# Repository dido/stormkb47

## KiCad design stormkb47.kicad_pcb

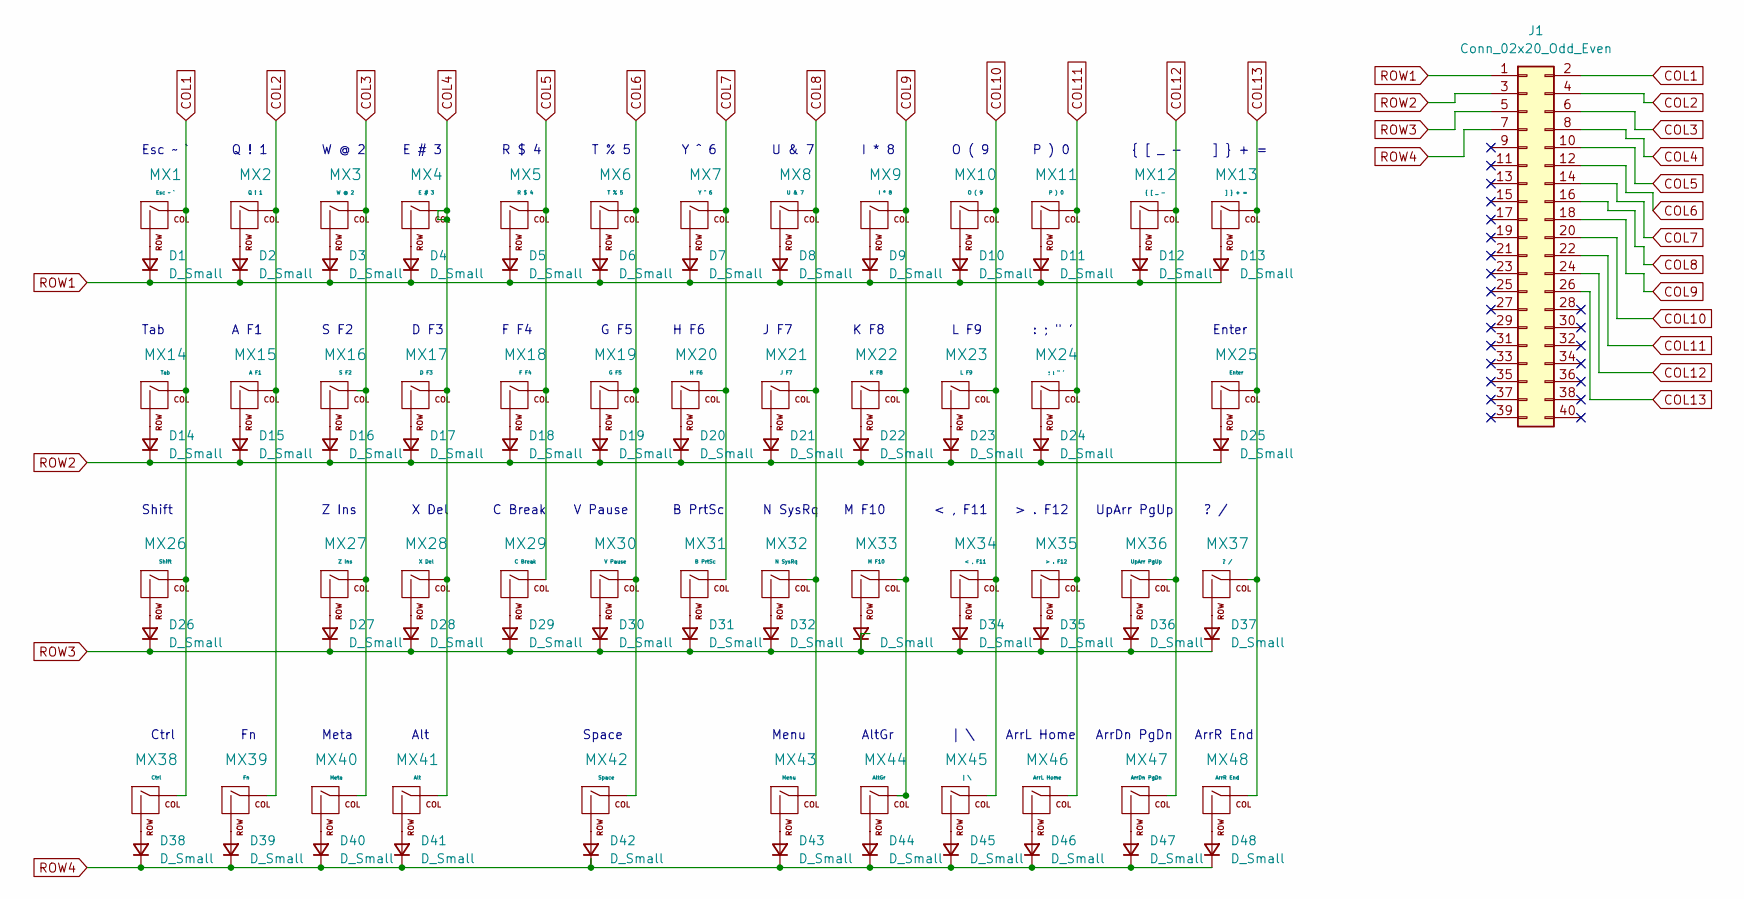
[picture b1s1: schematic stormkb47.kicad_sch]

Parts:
D1, D2, D3, D4, D5, D6, D7, D8, D9, D10, D11, D12, D13, D14, D15, D16, D17, D18, D19, D20, D21, D22, D23, D24, D25, D26, D27, D28, D29, D30, D31, D32, D33, D34, D35, D36, D37, D38, D39, D40, D41, D42, D43, D44, D45, D46, D47, D48: D_Small; D_SOD-123
J1: Conn_02x20_Odd_Even; PinSocket_2x20_P2.54mm_Vertical
MX1: Esc ~ `; MX-1U-NoLED
MX2: Q ! 1; MX-1U-NoLED
MX3: W @ 2; MX-1U-NoLED
MX4: E # 3; MX-1U-NoLED
MX5: R $ 4; MX-1U-NoLED
MX6: T % 5; MX-1U-NoLED
MX7: Y ^ 6; MX-1U-NoLED
MX8: U & 7; MX-1U-NoLED
MX9: I * 8; MX-1U-NoLED
MX10: O ( 9; MX-1U-NoLED
MX11: P ) 0; MX-1U-NoLED
MX12: { [ _ -; MX-1U-NoLED
MX13: ] } + =; MX-1U-NoLED
MX14: Tab; MX-1.5U-NoLED
MX15: A F1; MX-1U-NoLED
MX16: S F2; MX-1U-NoLED
MX17: D F3; MX-1U-NoLED
MX18: F F4; MX-1U-NoLED
MX19: G F5; MX-1U-NoLED
MX20: H F6; MX-1U-NoLED
MX21: J F7; MX-1U-NoLED
MX22: K F8; MX-1U-NoLED
MX23: L F9; MX-1U-NoLED
MX24: ; : " '; MX-1U-NoLED
MX25: Enter; MX-1.5U-NoLED
MX26: Shift; MX-2U-NoLED
MX27: Z Ins; MX-1U-NoLED
MX28: X Del; MX-1U-NoLED
MX29: C Break; MX-1U-NoLED
MX30: V Pause; MX-1U-NoLED
MX31: B PrtSc; MX-1U-NoLED
MX32: N SysRq; MX-1U-NoLED
MX33: M F10; MX-1U-NoLED
MX34: < , F11; MX-1U-NoLED
MX35: > . F12; MX-1U-NoLED
MX36: UpArr PgUp; MX-1U-NoLED
MX37: ? /; MX-1U-NoLED
MX38: Ctrl; MX-1U-NoLED
MX39: Fn; MX-1U-NoLED
MX40: Meta; MX-1U-NoLED
MX41: Alt; MX-1U-NoLED
MX42: Space; MX-3U-NoLED
MX43: Menu; MX-1U-NoLED
MX44: AltGr; MX-1U-NoLED
MX45: | \; MX-1U-NoLED
MX46: ArrL Home; MX-1U-NoLED
MX47: ArrDn PgDn; MX-1U-NoLED
MX48: ArrR End; MX-1U-NoLED

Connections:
COL1: J1.2, MX1.1 (COL), MX14.1 (COL), MX26.1 (COL), MX38.1 (COL)
COL2: J1.4, MX2.1 (COL), MX15.1 (COL), MX39.1 (COL)
COL3: J1.6, MX3.1 (COL), MX16.1 (COL), MX27.1 (COL), MX40.1 (COL)
COL4: J1.8, MX4.1 (COL), MX17.1 (COL), MX28.1 (COL), MX41.1 (COL)
COL5: J1.10, MX5.1 (COL), MX18.1 (COL), MX29.1 (COL)
COL6: J1.12, MX6.1 (COL), MX19.1 (COL), MX30.1 (COL), MX42.1 (COL)
COL7: J1.14, MX7.1 (COL), MX20.1 (COL), MX31.1 (COL)
COL8: J1.16, MX8.1 (COL), MX21.1 (COL), MX32.1 (COL), MX43.1 (COL)
COL9: J1.18, MX9.1 (COL), MX22.1 (COL), MX33.1 (COL), MX44.1 (COL)
COL10: J1.20, MX10.1 (COL), MX23.1 (COL), MX34.1 (COL), MX45.1 (COL)
COL11: J1.22, MX11.1 (COL), MX24.1 (COL), MX35.1 (COL), MX46.1 (COL)
COL12: J1.24, MX12.1 (COL), MX36.1 (COL), MX47.1 (COL)
COL13: J1.26, MX13.1 (COL), MX25.1 (COL), MX37.1 (COL), MX48.1 (COL)
unnamed: D1.2 (A), MX1.2 (ROW)
unnamed: D2.2 (A), MX2.2 (ROW)
unnamed: D3.2 (A), MX3.2 (ROW)
unnamed: D4.2 (A), MX4.2 (ROW)
unnamed: D5.2 (A), MX5.2 (ROW)
unnamed: D6.2 (A), MX6.2 (ROW)
unnamed: D7.2 (A), MX7.2 (ROW)
unnamed: D8.2 (A), MX8.2 (ROW)
unnamed: D9.2 (A), MX9.2 (ROW)
unnamed: D10.2 (A), MX10.2 (ROW)
unnamed: D11.2 (A), MX11.2 (ROW)
unnamed: D12.2 (A), MX12.2 (ROW)
unnamed: D13.2 (A), MX13.2 (ROW)
unnamed: D14.2 (A), MX14.2 (ROW)
unnamed: D15.2 (A), MX15.2 (ROW)
unnamed: D16.2 (A), MX16.2 (ROW)
unnamed: D17.2 (A), MX17.2 (ROW)
unnamed: D18.2 (A), MX18.2 (ROW)
unnamed: D19.2 (A), MX19.2 (ROW)
unnamed: D20.2 (A), MX20.2 (ROW)
unnamed: D21.2 (A), MX21.2 (ROW)
unnamed: D22.2 (A), MX22.2 (ROW)
unnamed: D23.2 (A), MX23.2 (ROW)
unnamed: D24.2 (A), MX24.2 (ROW)
unnamed: D25.2 (A), MX25.2 (ROW)
unnamed: D26.2 (A), MX26.2 (ROW)
unnamed: D27.2 (A), MX27.2 (ROW)
unnamed: D28.2 (A), MX28.2 (ROW)
unnamed: D29.2 (A), MX29.2 (ROW)
unnamed: D30.2 (A), MX30.2 (ROW)
unnamed: D31.2 (A), MX31.2 (ROW)
unnamed: D32.2 (A), MX32.2 (ROW)
unnamed: D33.2 (A), MX33.2 (ROW)
unnamed: D34.2 (A), MX34.2 (ROW)
unnamed: D35.2 (A), MX35.2 (ROW)
unnamed: D36.2 (A), MX36.2 (ROW)
unnamed: D37.2 (A), MX37.2 (ROW)
unnamed: D38.2 (A), MX38.2 (ROW)
unnamed: D39.2 (A), MX39.2 (ROW)
unnamed: D40.2 (A), MX40.2 (ROW)
unnamed: D41.2 (A), MX41.2 (ROW)
unnamed: D42.2 (A), MX42.2 (ROW)
unnamed: D43.2 (A), MX43.2 (ROW)
unnamed: D44.2 (A), MX44.2 (ROW)
unnamed: D45.2 (A), MX45.2 (ROW)
unnamed: D46.2 (A), MX46.2 (ROW)
unnamed: D47.2 (A), MX47.2 (ROW)
unnamed: D48.2 (A), MX48.2 (ROW)
ROW1: D1.1 (K), D2.1 (K), D3.1 (K), D4.1 (K), D5.1 (K), D6.1 (K), D7.1 (K), D8.1 (K), D9.1 (K), D10.1 (K), D11.1 (K), D12.1 (K), D13.1 (K), J1.1
ROW2: D14.1 (K), D15.1 (K), D16.1 (K), D17.1 (K), D18.1 (K), D19.1 (K), D20.1 (K), D21.1 (K), D22.1 (K), D23.1 (K), D24.1 (K), D25.1 (K), J1.3
ROW3: D26.1 (K), D27.1 (K), D28.1 (K), D29.1 (K), D30.1 (K), D31.1 (K), D32.1 (K), D33.1 (K), D34.1 (K), D35.1 (K), D36.1 (K), D37.1 (K), J1.5
ROW4: D38.1 (K), D39.1 (K), D40.1 (K), D41.1 (K), D42.1 (K), D43.1 (K), D44.1 (K), D45.1 (K), D46.1 (K), D47.1 (K), D48.1 (K), J1.7

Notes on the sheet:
M F10
H F6
G F5
Tab
I * 8
A F1
UpArr PgUp
Alt
| \
{ [ _ -
> . F12
Esc ~ `
W @ 2
B PrtSc
? /
F F4
: ; " '
R $ 4
U & 7
Enter
Meta
J F7
] } + =
X Del
V Pause
ArrDn PgDn
< , F11
S F2
Q ! 1
T % 5
Y ^ 6
N SysRq
Menu
L F9
ArrR End
O ( 9
Ctrl
Z Ins
E # 3
ArrL Home

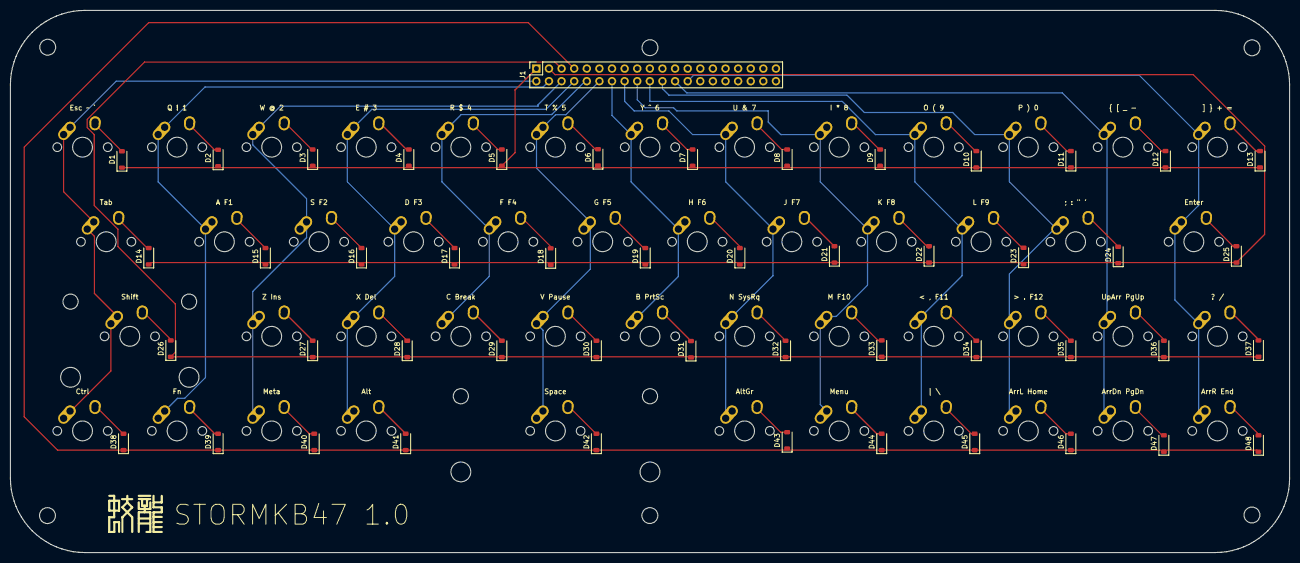
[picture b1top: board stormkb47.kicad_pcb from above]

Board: 2 copper layers, 257.7 x 109.2 mm, 97 parts (0 on the bottom side), 65 nets.

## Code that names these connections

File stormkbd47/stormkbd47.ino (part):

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// Arduino pins associated with columns and rows for the
// keyboard matrix

const byte col1 = A4;
const byte col2 = 2;
const byte col3 = 3;
const byte col4 = 4;
const byte col5 = 5;
const byte col6 = 6;
const byte col7 = 7;
const byte col8 = 8;
const byte col9 = 9;
const byte col10 = 10;
const byte col11 = 11;
const byte col12 = 12;
const byte col13 = 13;

const byte row1 = A0;
const byte row2 = A1;
const byte row3 = A2;
const byte row4 = A3;

#define USE_KEYBOARD
#define USE_LED
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  digitalWrite(row3, LOW); // turn off pullup
  digitalWrite(row4, LOW); // turn off pullup

  pinMode(row1, INPUT); // High-Z
  pinMode(row2, INPUT); // High-Z 
  pinMode(row3, INPUT); // High-Z
  pinMode(row4, INPUT); // High-Z
  
  // Rows are inputs with pullups
  
  pinMode(row1, INPUT);
  pinMode(row2, INPUT);
  pinMode(row3, INPUT);
  pinMode(row4, INPUT);

  pinMode(col1, INPUT);
  pinMode(col2, INPUT);
  pinMode(col3, INPUT);
  pinMode(col4, INPUT);
  pinMode(col5, INPUT);
  pinMode(col6, INPUT);
  pinMode(col7, INPUT);
  pinMode(col8, INPUT);
  pinMode(col9, INPUT);
  pinMode(col10, INPUT);
  pinMode(col11, INPUT);
  pinMode(col12, INPUT);
  pinMode(col13, INPUT);

  digitalWrite(col1, HIGH); // set pullup
  digitalWrite(col2, HIGH); // set pullup
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  unsigned char mods = 0x00;
  delay(10);

  pinMode(row1, OUTPUT); 
  digitalWrite(row1, LOW);
  
  if (digitalRead(col1)==0) { key = KEY_ESC; }   // Esc ` ~
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  if (digitalRead(col12)==0) { key = '['; }  // { [ } ]
  if (digitalRead(col13)==0) { key = KEY_BACKSPACE; }  // Backspace Del

  pinMode(row1, INPUT); 
  pinMode(row2, OUTPUT); 
  digitalWrite(row2, LOW);

  if (digitalRead(col1)==0) { key = KEY_TAB; }  // Tab
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  if (digitalRead(col12)==0) {  } // (not used)
  if (digitalRead(col13)==0) { key = KEY_RETURN; } // Enter

  pinMode(row2, INPUT); 
  pinMode(row3, OUTPUT); 
  digitalWrite(row3, LOW);

  if (digitalRead(col1)==0) { mods |= MOD_SHIFT; } // Shift
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  if (digitalRead(col12)==0) { key = KEY_UP_ARROW; } // UpArrow PgUp
  if (digitalRead(col13)==0) { key = '/'; } // ? /
 
  pinMode(row3, INPUT); 
  pinMode(row4, OUTPUT); 
  digitalWrite(row4, LOW);

  if (digitalRead(col1)==0) { mods |= MOD_CTRL; } // Ctrl
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  if (digitalRead(col11)==0) { key = KEY_LEFT_ARROW; } // Left Arrow Home
  if (digitalRead(col12)==0) { key = KEY_DOWN_ARROW; } // Down Arrow PgDn
  if (digitalRead(col13)==0) { key = KEY_RIGHT_ARROW; } // Right Arrow End
  pinMode(row4, INPUT); 

  // Debounce
  if (!(dbkey == key && dbmods == mods))
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  unsigned int keys[48];
  unsigned int *keyptr = keys;

  pinMode(row1, OUTPUT); 
  digitalWrite(row1, LOW);
  
  if (digitalRead(col1)==0) { *keyptr++ = 0x11; }   // Esc ` ~
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  if (digitalRead(col12)==0) { *keyptr++ = 0x1c; }  // { [ __ -
  if (digitalRead(col13)==0) { *keyptr++ = 0x1d; }  // }] + =

  pinMode(row1, INPUT); 
  pinMode(row2, OUTPUT); 
  digitalWrite(row2, LOW);

  if (digitalRead(col1)==0) { *keyptr++ = 0x21; }  // Tab
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  if (digitalRead(col12)==0) { *keyptr++ = 0x2c; } // (not used)
  if (digitalRead(col13)==0) { *keyptr++ = 0x2d; } // Enter

  pinMode(row2, INPUT); 
  pinMode(row3, OUTPUT); 
  digitalWrite(row3, LOW);

  if (digitalRead(col1)==0) { *keyptr++ = 0x31; } // Shift
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  if (digitalRead(col12)==0) { *keyptr++ = 0x3c; } // UpArrow PgUp
  if (digitalRead(col13)==0) { *keyptr++ = 0x3d; } // ? /
 
  pinMode(row3, INPUT); 
  pinMode(row4, OUTPUT); 
  digitalWrite(row4, LOW);

  if (digitalRead(col1)==0) { *keyptr++ = 0x41; } // Ctrl
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  if (digitalRead(col11)==0) { *keyptr++ = 0x4b; } // Left Arrow Home
  if (digitalRead(col12)==0) { *keyptr++ = 0x4c; } // Down Arrow PgDn
  if (digitalRead(col13)==0) { *keyptr++ = 0x4d; } // Right Arrow End
  pinMode(row4, INPUT); 

  if (keyptr > keys) {
    Serial.print("Scancodes: ");
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
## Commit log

2023-12-27 modifications
2023-12-27 ignore backups and lock files
2023-12-27 align keys and change labels to read the keycaps
2023-12-27 diodes placed
2023-12-27 routed all traces
2023-12-27 fixed missing connections
2023-12-27 add menu button
2023-12-27 use proper-sized footprints for wide keys and add menu button
2023-12-27 move spacebar and add 48th key
2023-12-27 logo and annotations on silkscreen layer
2023-12-27 SVG version of keyboard plate
2023-12-28 final changes before production
2024-01-12 Arduino firmware
2024-02-14 - _ swapped with | \
2024-02-14 modifications to button position of trackpoint module
2024-02-14 original plate without extension and trackpoint holes
2024-02-14 3D printed plate extrusion (FreeCAD)
2024-02-14 reverse backslash/bar and underscore minus
2024-02-14 CERN OHL Permissive + GPLv3
2024-02-14 add GPLv3 license blurb

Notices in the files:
stormkbd47/stormkbd47.ino:
Copyright (C) 2024 Rafael David R. Sevilla
This program is free software: you can redistribute it and/or modify
it under the terms of the GNU General Public License as published by
the Free Software Foundation, either version 3 of the License, or
(at your option) any later version.
